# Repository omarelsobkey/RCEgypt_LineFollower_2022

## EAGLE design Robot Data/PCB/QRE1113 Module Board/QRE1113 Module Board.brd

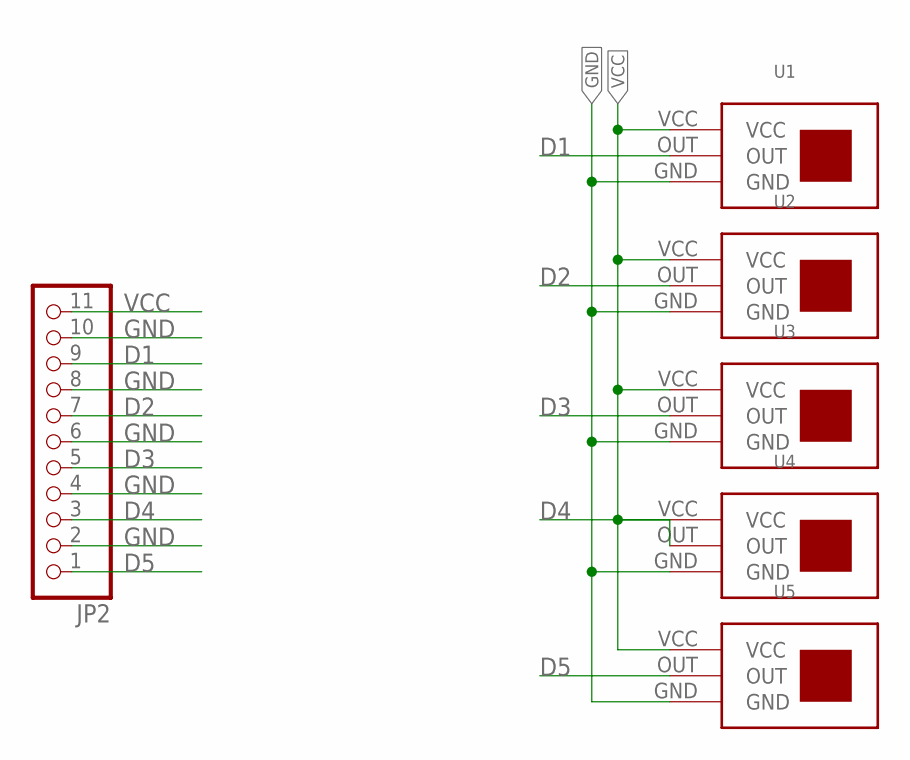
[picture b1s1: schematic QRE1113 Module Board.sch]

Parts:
JP2: PINHD-1X11/90; 1X11/90
U1, U2, U3, U4, U5: QRE1113

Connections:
D1: JP2.9, U1.OUT
D2: JP2.7, U2.OUT
D3: JP2.5, U3.OUT
D4: JP2.3, U4.OUT
D5: JP2.1, U5.OUT
GND: JP2.2, JP2.4, JP2.6, JP2.8, JP2.10, U1.GND, U2.GND, U3.GND, U4.GND, U5.GND
VCC: JP2.11, U1.VCC, U2.VCC, U3.VCC, U4.VCC, U5.VCC

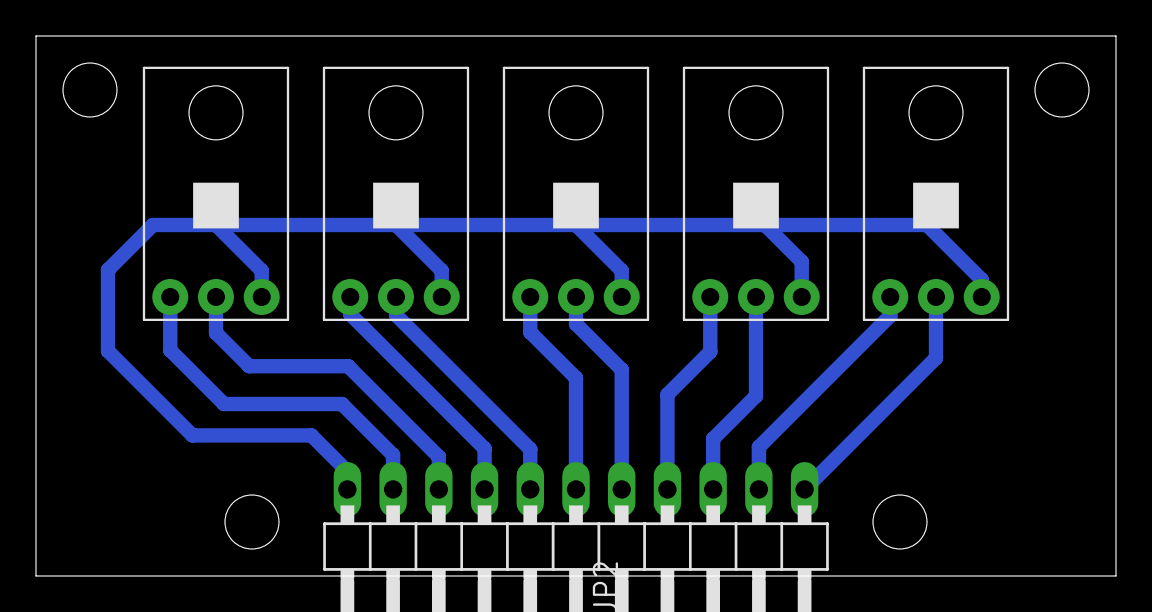
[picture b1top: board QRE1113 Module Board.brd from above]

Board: 2 copper layers, 60.0 x 30.0 mm, 6 parts (0 on the bottom side), 7 nets.

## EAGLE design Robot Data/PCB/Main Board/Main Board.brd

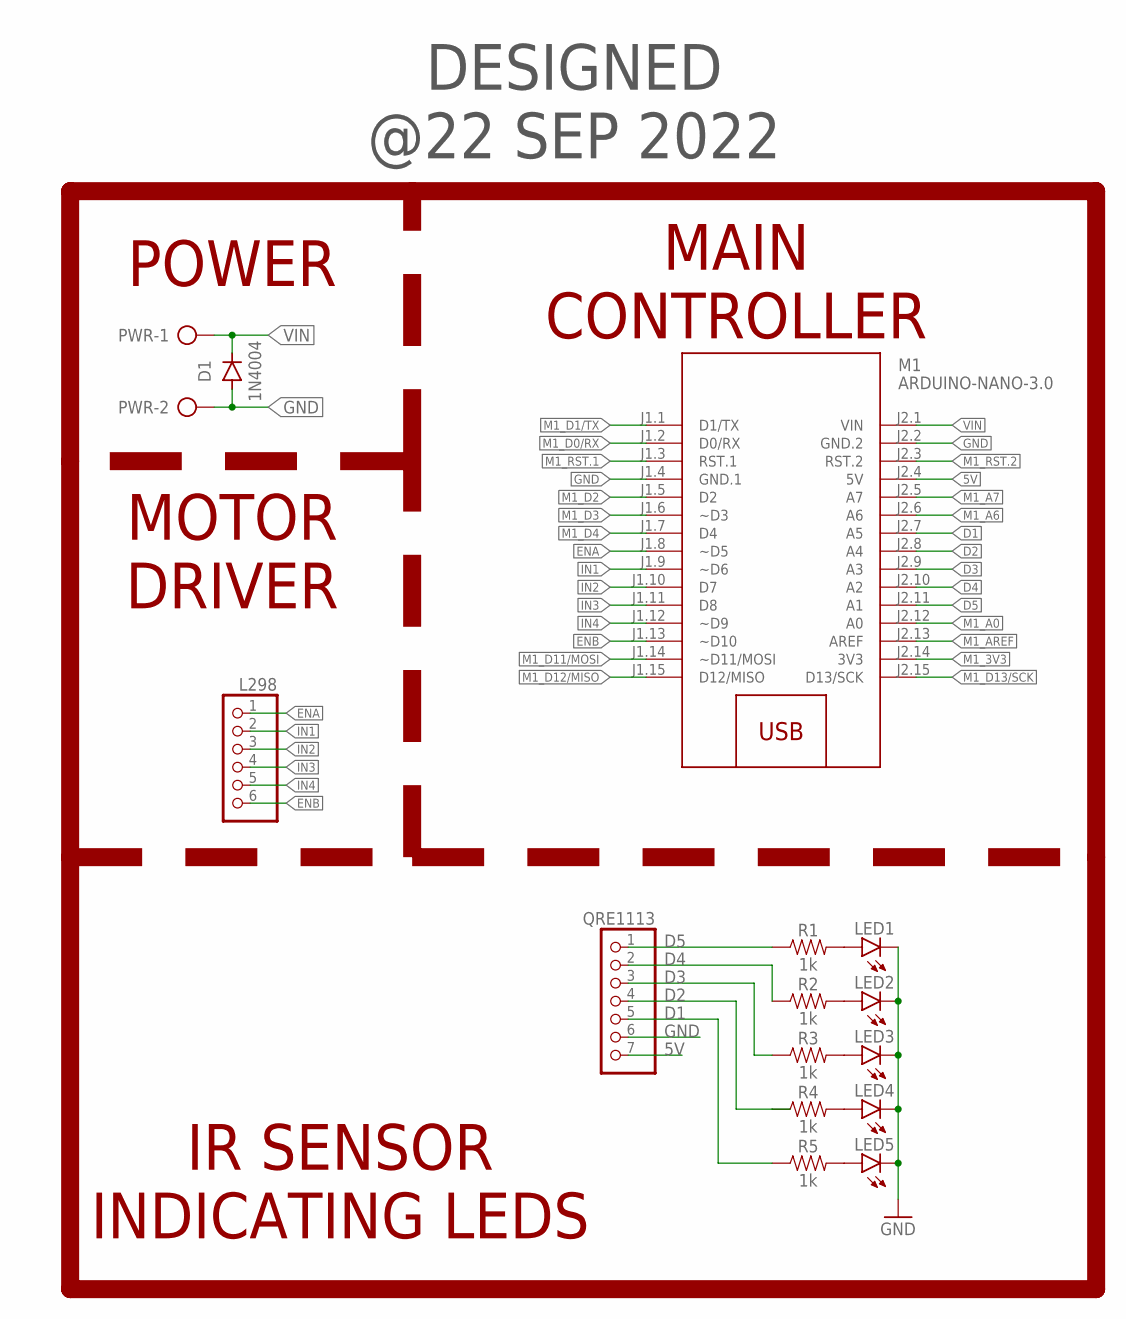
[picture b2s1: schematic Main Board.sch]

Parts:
D1: 1N4004; DO41-10
L298: PINHD-1X6; 1X06
LED1, LED2, LED3, LED4, LED5: LED5MM
M1: ARDUINO-NANO-3.0
PWR: 2P
QRE1113: PINHD-1X7/90; 1X07/90
R1, R2, R3, R4, R5: 1k; AXIAL-0.3

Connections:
5V: M1.J2.4 (5V), QRE1113.7
D1: M1.J2.7 (A5), QRE1113.5, R5.P$1 (1)
D2: M1.J2.8 (A4), QRE1113.4, R4.P$1 (1)
D3: M1.J2.9 (A3), QRE1113.3, R3.P$1 (1)
D4: M1.J2.10 (A2), QRE1113.2, R2.P$1 (1)
D5: M1.J2.11 (A1), QRE1113.1, R1.P$1 (1)
ENA: L298.1, M1.J1.8 (~D5)
ENB: L298.6, M1.J1.13 (~D10)
GND: D1.A, LED1.K (C), LED2.K (C), LED3.K (C), LED4.K (C), LED5.K (C), M1.J1.4 (GND.1), M1.J2.2 (GND.2), PWR.2, QRE1113.6
IN1: L298.2, M1.J1.9 (~D6)
IN2: L298.3, M1.J1.10 (D7)
IN3: L298.4, M1.J1.11 (D8)
IN4: L298.5, M1.J1.12 (~D9)
M1_3V3: M1.J2.14 (3V3)
M1_A0: M1.J2.12 (A0)
M1_A6: M1.J2.6 (A6)
M1_A7: M1.J2.5 (A7)
M1_AREF: M1.J2.13 (AREF)
M1_D0/RX: M1.J1.2 (D0/RX)
M1_D1/TX: M1.J1.1 (D1/TX)
M1_D2: M1.J1.5 (D2)
M1_D3: M1.J1.6 (~D3)
M1_D4: M1.J1.7 (D4)
M1_D11/MOSI: M1.J1.14 (~D11/MOSI)
M1_D12/MISO: M1.J1.15 (D12/MISO)
M1_D13/SCK: M1.J2.15 (D13/SCK)
M1_RST.1: M1.J1.3 (RST.1)
M1_RST.2: M1.J2.3 (RST.2)
unnamed: LED1.A, R1.P$2 (2)
unnamed: LED2.A, R2.P$2 (2)
unnamed: LED3.A, R3.P$2 (2)
unnamed: LED4.A, R4.P$2 (2)
unnamed: LED5.A, R5.P$2 (2)
VIN: D1.C, M1.J2.1 (VIN), PWR.1

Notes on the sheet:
POWER
MAIN CONTROLLER
MOTOR DRIVER
IR SENSOR INDICATING LEDS
DESIGNED @22 SEP 2022

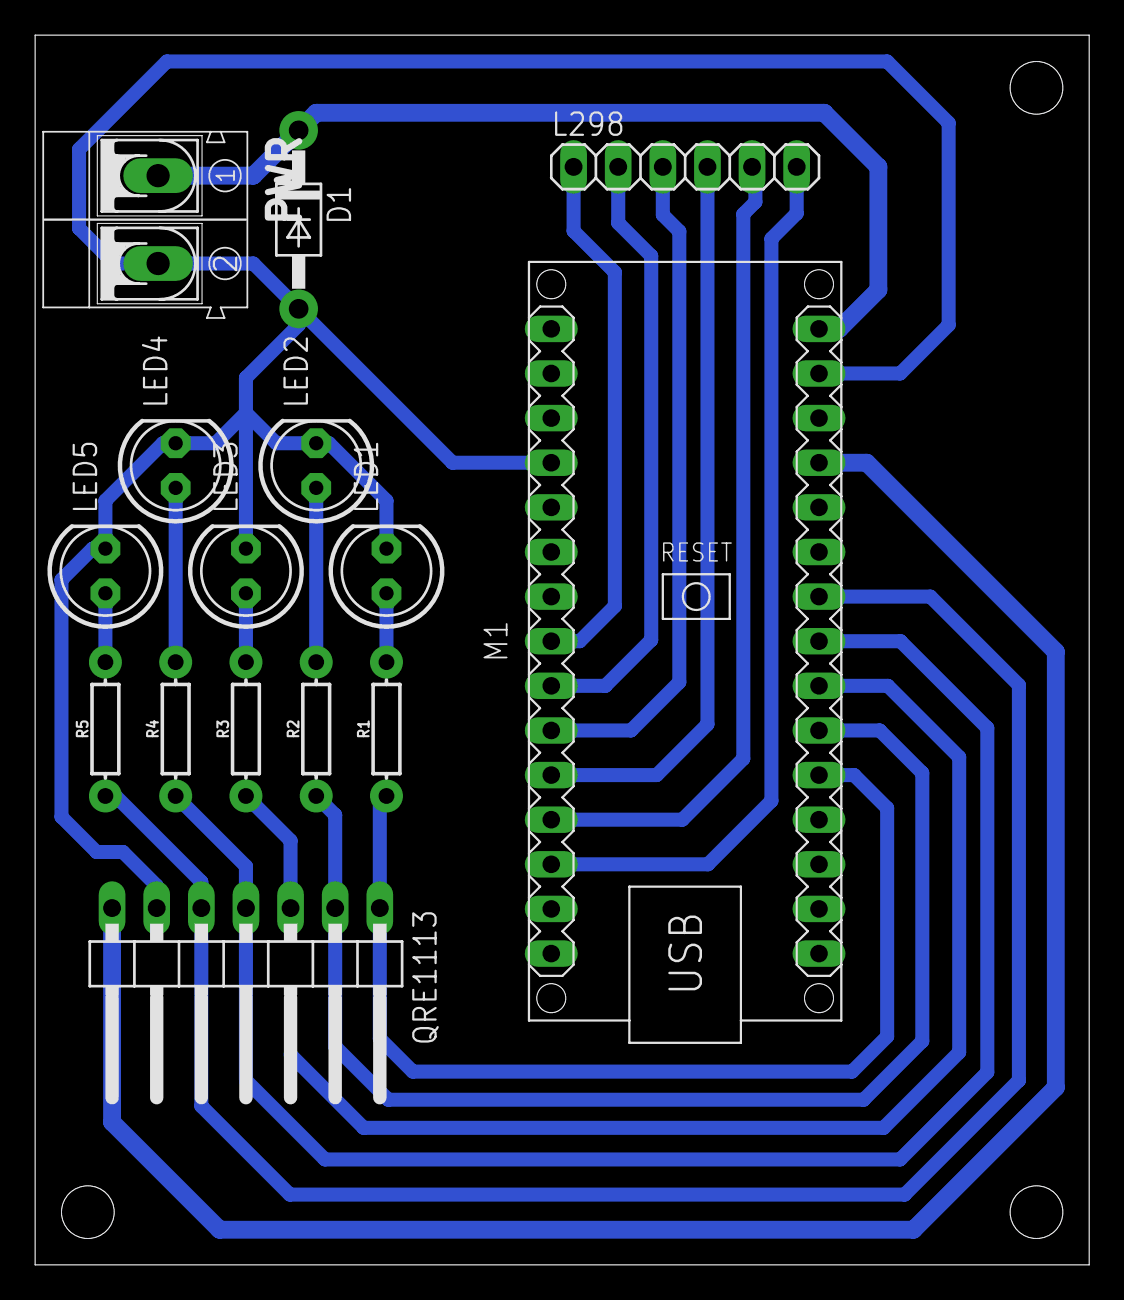
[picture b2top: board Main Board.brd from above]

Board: 2 copper layers, 60.0 x 70.0 mm, 15 parts (0 on the bottom side), 19 nets.

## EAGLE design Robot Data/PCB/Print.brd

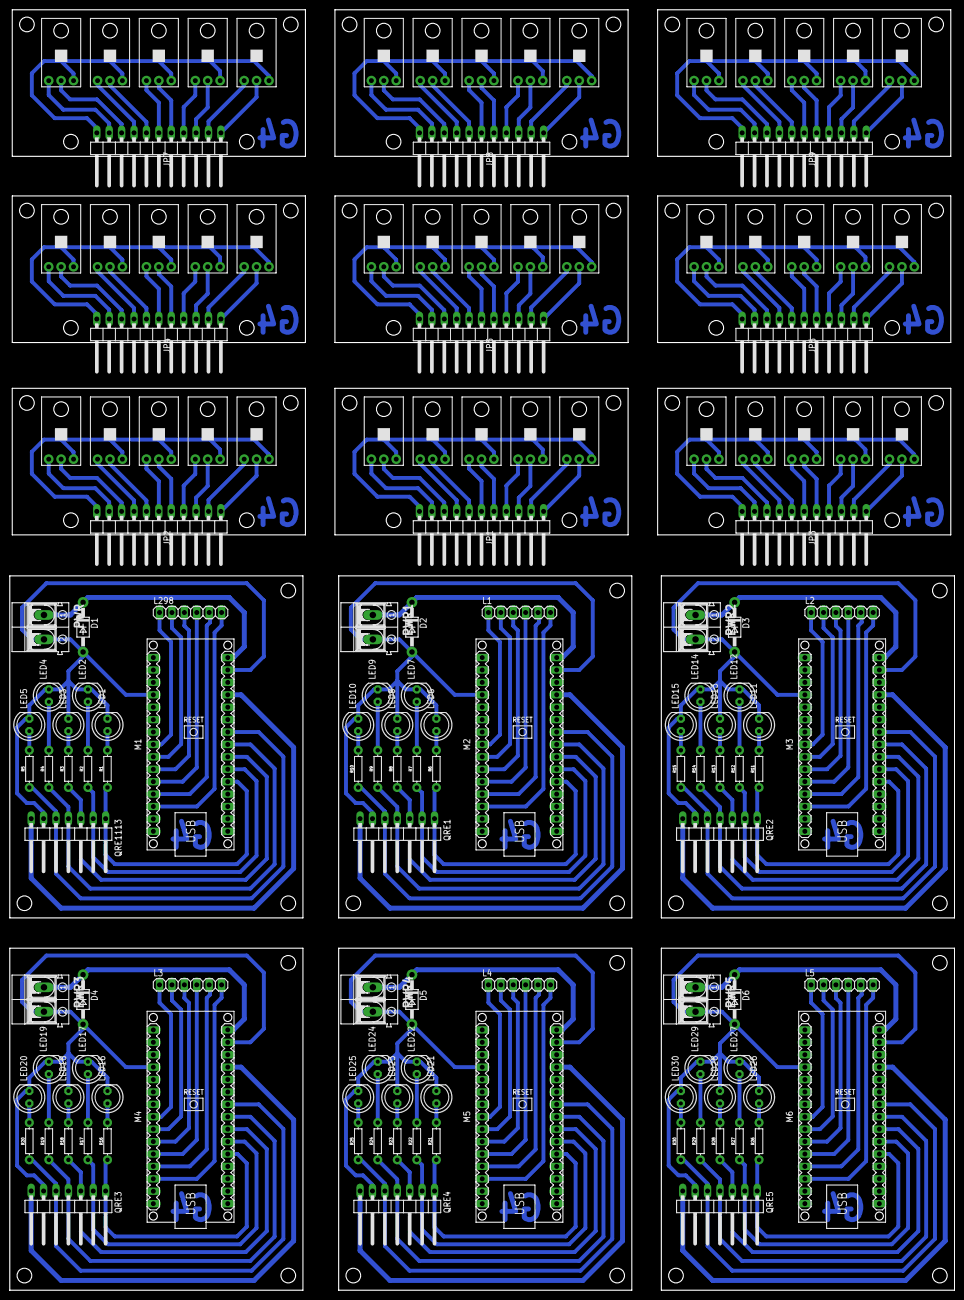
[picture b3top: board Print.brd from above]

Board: 2 copper layers, 193.3 x 262.1 mm, 144 parts (0 on the bottom side), 177 nets.

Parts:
D1, D2, D3, D4, D5, D6: 1N4004; DO41-10
JP1, JP2, JP3, JP4, JP5, JP6, JP7, JP8, JP9: 1X11/90
L1, L2, L3, L4, L5, L298: 1X06
LED1, LED2, LED3, LED4, LED5, LED6, LED7, LED8, LED9, LED10, LED11, LED12, LED13, LED14, LED15, LED16, LED17, LED18, LED19, LED20, LED21, LED22, LED23, LED24, LED25, LED26, LED27, LED28, LED29, LED30: LED5MM
M1, M2, M3, M4, M5, M6: ARDUINO-NANO-3.0
PWR, PWR1, PWR2, PWR3, PWR4, PWR5: 2P
QRE1, QRE2, QRE3, QRE4, QRE5, QRE1113: 1X07/90
R1, R2, R3, R4, R5, R6, R7, R8, R9, R10, R11, R12, R13, R14, R15, R16, R17, R18, R19, R20, R21, R22, R23, R24, R25, R26, R27, R28, R29, R30: 1k; AXIAL-0.3
U1, U2, U3, U4, U5, U6, U7, U8, U9, U10, U11, U12, U13, U14, U15, U16, U17, U18, U19, U20, U21, U22, U23, U24, U25, U26, U27, U28, U29, U30, U31, U32, U33, U34, U35, U36, U37, U38, U39, U40, U41, U42, U43, U44, U45: QRE1113

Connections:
5V: M1.J2.4, QRE1113.7
5V1: M2.J2.4, QRE1.7
5V2: M3.J2.4, QRE2.7
5V3: M4.J2.4, QRE3.7
5V4: M5.J2.4, QRE4.7
5V5: M6.J2.4, QRE5.7
D1: JP2.9, U1.OUT
D2: JP2.7, U2.OUT
D3: JP2.5, U3.OUT
D4: JP2.3, U4.OUT
D5: JP2.1, U5.OUT
D6: M1.J2.10, QRE1113.2, R2.P$1
D7: M1.J2.11, QRE1113.1, R1.P$1
D8: M1.J2.7, QRE1113.5, R5.P$1
D9: M1.J2.8, QRE1113.4, R4.P$1
D10: M1.J2.9, QRE1113.3, R3.P$1
D11: M2.J2.10, QRE1.2, R7.P$1
D12: M2.J2.11, QRE1.1, R6.P$1
D13: M2.J2.7, QRE1.5, R10.P$1
D14: M2.J2.8, QRE1.4, R9.P$1
D15: M2.J2.9, QRE1.3, R8.P$1
D16: M3.J2.10, QRE2.2, R12.P$1
D17: M3.J2.11, QRE2.1, R11.P$1
D18: M3.J2.7, QRE2.5, R15.P$1
D19: M3.J2.8, QRE2.4, R14.P$1
D20: M3.J2.9, QRE2.3, R13.P$1
D21: M4.J2.10, QRE3.2, R17.P$1
D22: M4.J2.11, QRE3.1, R16.P$1
D23: M4.J2.7, QRE3.5, R20.P$1
D24: M4.J2.8, QRE3.4, R19.P$1
D25: M4.J2.9, QRE3.3, R18.P$1
D26: M5.J2.10, QRE4.2, R22.P$1
D27: M5.J2.11, QRE4.1, R21.P$1
D28: M5.J2.7, QRE4.5, R25.P$1
D29: M5.J2.8, QRE4.4, R24.P$1
D30: M5.J2.9, QRE4.3, R23.P$1
D31: M6.J2.10, QRE5.2, R27.P$1
D32: M6.J2.11, QRE5.1, R26.P$1
D33: M6.J2.7, QRE5.5, R30.P$1
D34: M6.J2.8, QRE5.4, R29.P$1
D35: M6.J2.9, QRE5.3, R28.P$1
D36: JP1.1, U10.OUT
D37: JP1.3, U9.OUT
D38: JP1.5, U8.OUT
D39: JP1.7, U7.OUT
D40: JP1.9, U6.OUT
D41: JP3.1, U15.OUT
D42: JP3.3, U14.OUT
D43: JP3.5, U13.OUT
D44: JP3.7, U12.OUT
D45: JP3.9, U11.OUT
D46: JP4.1, U20.OUT
D47: JP4.3, U19.OUT
D48: JP4.5, U18.OUT
D49: JP4.7, U17.OUT
D50: JP4.9, U16.OUT
D51: JP5.1, U25.OUT
D52: JP5.3, U24.OUT
D53: JP5.5, U23.OUT
D54: JP5.7, U22.OUT
D55: JP5.9, U21.OUT
D56: JP6.1, U30.OUT
D57: JP6.3, U29.OUT
D58: JP6.5, U28.OUT
D59: JP6.7, U27.OUT
D60: JP6.9, U26.OUT
D61: JP7.1, U35.OUT
D62: JP7.3, U34.OUT
D63: JP7.5, U33.OUT
D64: JP7.7, U32.OUT
D65: JP7.9, U31.OUT
D66: JP8.1, U40.OUT
D67: JP8.3, U39.OUT
D68: JP8.5, U38.OUT
D69: JP8.7, U37.OUT
D70: JP8.9, U36.OUT
D71: JP9.1, U45.OUT
D72: JP9.3, U44.OUT
D73: JP9.5, U43.OUT
D74: JP9.7, U42.OUT
D75: JP9.9, U41.OUT
ENA: L298.1, M1.J1.8
ENA1: L1.1, M2.J1.8
ENA2: L2.1, M3.J1.8
ENA3: L3.1, M4.J1.8
ENA4: L4.1, M5.J1.8
ENA5: L5.1, M6.J1.8
ENB: L298.6, M1.J1.13
ENB1: L1.6, M2.J1.13
ENB2: L2.6, M3.J1.13
ENB3: L3.6, M4.J1.13
ENB4: L4.6, M5.J1.13
ENB5: L5.6, M6.J1.13
GND: JP2.2, JP2.4, JP2.6, JP2.8, JP2.10, U1.GND, U2.GND, U3.GND, U4.GND, U5.GND
GND1: D1.A, LED1.K, LED2.K, LED3.K, LED4.K, LED5.K, M1.J1.4, M1.J2.2, PWR.2, QRE1113.6
GND2: D2.A, LED6.K, LED7.K, LED8.K, LED9.K, LED10.K, M2.J1.4, M2.J2.2, PWR1.2, QRE1.6
GND3: D3.A, LED11.K, LED12.K, LED13.K, LED14.K, LED15.K, M3.J1.4, M3.J2.2, PWR2.2, QRE2.6
GND4: D4.A, LED16.K, LED17.K, LED18.K, LED19.K, LED20.K, M4.J1.4, M4.J2.2, PWR3.2, QRE3.6
GND5: D5.A, LED21.K, LED22.K, LED23.K, LED24.K, LED25.K, M5.J1.4, M5.J2.2, PWR4.2, QRE4.6
GND6: D6.A, LED26.K, LED27.K, LED28.K, LED29.K, LED30.K, M6.J1.4, M6.J2.2, PWR5.2, QRE5.6
GND7: JP1.2, JP1.4, JP1.6, JP1.8, JP1.10, U6.GND, U7.GND, U8.GND, U9.GND, U10.GND
GND8: JP3.2, JP3.4, JP3.6, JP3.8, JP3.10, U11.GND, U12.GND, U13.GND, U14.GND, U15.GND
GND9: JP4.2, JP4.4, JP4.6, JP4.8, JP4.10, U16.GND, U17.GND, U18.GND, U19.GND, U20.GND
GND10: JP5.2, JP5.4, JP5.6, JP5.8, JP5.10, U21.GND, U22.GND, U23.GND, U24.GND, U25.GND
GND11: JP6.2, JP6.4, JP6.6, JP6.8, JP6.10, U26.GND, U27.GND, U28.GND, U29.GND, U30.GND
GND12: JP7.2, JP7.4, JP7.6, JP7.8, JP7.10, U31.GND, U32.GND, U33.GND, U34.GND, U35.GND
GND13: JP8.2, JP8.4, JP8.6, JP8.8, JP8.10, U36.GND, U37.GND, U38.GND, U39.GND, U40.GND
GND14: JP9.2, JP9.4, JP9.6, JP9.8, JP9.10, U41.GND, U42.GND, U43.GND, U44.GND, U45.GND
IN1: L298.2, M1.J1.9
IN2: L298.3, M1.J1.10
IN3: L298.4, M1.J1.11
IN4: L298.5, M1.J1.12
IN5: L1.2, M2.J1.9
IN6: L1.3, M2.J1.10
IN7: L1.4, M2.J1.11
IN8: L1.5, M2.J1.12
IN9: L2.2, M3.J1.9
IN10: L2.3, M3.J1.10
IN11: L2.4, M3.J1.11
IN12: L2.5, M3.J1.12
IN13: L3.2, M4.J1.9
IN14: L3.3, M4.J1.10
IN15: L3.4, M4.J1.11
IN16: L3.5, M4.J1.12
IN17: L4.2, M5.J1.9
IN18: L4.3, M5.J1.10
IN19: L4.4, M5.J1.11
IN20: L4.5, M5.J1.12
IN21: L5.2, M6.J1.9
IN22: L5.3, M6.J1.10
IN23: L5.4, M6.J1.11
IN24: L5.5, M6.J1.12
unnamed: LED1.A, R1.P$2
unnamed: LED2.A, R2.P$2
unnamed: LED3.A, R3.P$2
unnamed: LED4.A, R4.P$2
unnamed: LED5.A, R5.P$2
unnamed: LED6.A, R6.P$2
unnamed: LED7.A, R7.P$2
unnamed: LED8.A, R8.P$2
unnamed: LED9.A, R9.P$2
unnamed: LED10.A, R10.P$2
unnamed: LED11.A, R11.P$2
unnamed: LED12.A, R12.P$2
unnamed: LED13.A, R13.P$2
unnamed: LED14.A, R14.P$2
unnamed: LED15.A, R15.P$2
unnamed: LED16.A, R16.P$2
unnamed: LED17.A, R17.P$2
unnamed: LED18.A, R18.P$2
unnamed: LED19.A, R19.P$2
unnamed: LED20.A, R20.P$2
unnamed: LED21.A, R21.P$2
unnamed: LED22.A, R22.P$2
unnamed: LED23.A, R23.P$2
unnamed: LED24.A, R24.P$2
unnamed: LED25.A, R25.P$2
unnamed: LED26.A, R26.P$2
unnamed: LED27.A, R27.P$2
unnamed: LED28.A, R28.P$2
unnamed: LED29.A, R29.P$2
unnamed: LED30.A, R30.P$2
VCC: JP2.11, U1.VCC, U2.VCC, U3.VCC, U4.VCC, U5.VCC
VCC1: JP1.11, U6.VCC, U7.VCC, U8.VCC, U9.VCC, U10.VCC
VCC2: JP3.11, U11.VCC, U12.VCC, U13.VCC, U14.VCC, U15.VCC
VCC3: JP4.11, U16.VCC, U17.VCC, U18.VCC, U19.VCC, U20.VCC
VCC4: JP5.11, U21.VCC, U22.VCC, U23.VCC, U24.VCC, U25.VCC
VCC5: JP6.11, U26.VCC, U27.VCC, U28.VCC, U29.VCC, U30.VCC
VCC6: JP7.11, U31.VCC, U32.VCC, U33.VCC, U34.VCC, U35.VCC
VCC7: JP8.11, U36.VCC, U37.VCC, U38.VCC, U39.VCC, U40.VCC
VCC8: JP9.11, U41.VCC, U42.VCC, U43.VCC, U44.VCC, U45.VCC
VIN: D1.C, M1.J2.1, PWR.1
VIN1: D2.C, M2.J2.1, PWR1.1
VIN2: D3.C, M3.J2.1, PWR2.1
VIN3: D4.C, M4.J2.1, PWR3.1
VIN4: D5.C, M5.J2.1, PWR4.1
VIN5: D6.C, M6.J2.1, PWR5.1

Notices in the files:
parts and their libraries:
Modules: Released under the Creative Commons Attribution 4.0 International License: http://creativecommons.org/licenses/by/4.0
SparkFun-Resistors: Licensing: Creative Commons ShareAlike 4.0 International - https://creativecommons.org/licenses/by-sa/4.0
